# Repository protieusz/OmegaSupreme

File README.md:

# OmegaSupreme
RP2040 integrated components with integrated PMW3360 trackball sensor &amp; PER56 encoder. The OmegaSupreme is inspired by Ariamelon's Kiwano VIK module and jfedor2's RP2040 and PMW3660 module. The RP2040 pins are fully broken out into either pads or ribbon connections. Design this for convienience and easier to design a keyboard pcb around the OmegaSupreme itself.
Current on print by JLCPCB. Cost is a little bit on the pricey side. Around $89 CAD with shipping included. SK6812 mini e was omitted from the assembly to keep the cost down.  Part of the reason behind being pricey was the use of 3 extended parts i.e. 2 ribbon connectors and 1 JSH connector.  [Gerber](https://github.com/protieusz/OmegaSupreme/tree/main/OmegaSupremeRev4) files will be posted once I tested it. As always print at your "OWN RISK".  I do not offer support. You can feel free to modify it as long as you credit me. Thanks.

# Note: Currently there are 2 versions of Omega Supreme. OmegaSupreme USB C & Non USB C Version using a C3 Unified USB C Daughterboard card

# OmegaSupreme got mentioned on https://kbd.news/Starship-Bubu-OmegaSupreme-2184.html

# Update: Nov 13, 2023: OmegaSupreme USB Version.
Uploaded OmegaSupreme USB Version files. This is my preferred OmegaSupreme version. This version's production file will include a converted json file from EasyEDA to KiCad pcb file.  Please print and assembly at your own risk. I have the PCBs printed and tested so it works. No support will be given. Please follow the license when you modify, use, etc. Thanks.

# Extra BOMs:

1 [PMW3360 Sensor for trackball](https://www.aliexpress.com/item/1005005355003386.html?spm=a2g0o.order_list.order_list_main.23.31a51802RLpcrc)

2 [C3 Unified USB C Daughterboard card](https://42keebs.eu/shop/parts/unified-daughterboard-c3-c4/?attribute_version=C3)

3 [M3 3mm standoffs](https://www.aliexpress.com/item/1005004127890102.html?spm=a2g0o.order_list.order_list_main.60.31a51802RLpcrc)

4 [M3 8mm screw, buy 6mm just in case](https://www.aliexpress.com/item/1005003733948224.html?spm=a2g0o.order_list.order_list_main.41.31a51802RLpcrc)

5 [MJ311 or MJ310 steel or ceramic ball bearings for the trackball support holder unit. Steel is slightly noisy and scratchy compared to ceramic. Test it out on your own](https://www.aliexpress.com/item/1005005334424631.html?spm=a2g0o.order_list.order_list_main.66.31a51802RLpcrc)

6 [RGBs SK6812](https://www.aliexpress.com/item/1005003636607308.html?spm=a2g0o.order_list.order_list_main.5.31a51802RLpcrc)

7 [Reset & Boot switches](https://www.aliexpress.com/item/4001317902663.html?spm=a2g0o.order_list.order_list_main.240.31a51802RLpcrc)

# OmegaSupreme USB Version Final Pics:

Back Side

Front & Back Side

# Update: Nov 12, 2023. 
Currently there are 2 versions of Omega Supreme. The Rev 4 with all the extended connectors and a USB C version that does not require a USB C daughterboard card. I printed both versions and I find that Rev 1 is very annoying since it needs a USB C daughterboard card.  Nowadays, the reliability of PCBA and PCB printing from China factories are not that good if you are doing small 5 PCBs prototyping.  In my experience PCBA can be hit and miss.  Even the USB C daughterboard card can be a miss also.  So in order to eliminate headaches, I use the Omega Supreme USB C version where everything is in one place. Easier to diagnostic if shit goes south.

# REV 4 has 2 copper plated holes for the trackball support mount on the PCB which was missed during REV 1 print.  This PCB picture is REV1 without the corrected copper plated mount holes.

# D- and D+ pins are switched so when you attach your usb c daughterboard card, please be caution.

# REV 4 render. I don't have funds to print anymore.

# REV 1

# REV 3 Forgot to add M3 plated mounts for the trackball support and added RGB DOUT, 5v and GND for the last RGB on the OmegaSupreme

# License

</a></p>

You are free to:

Share — copy and redistribute the material in any medium or format

Adapt — remix, transform, and build upon the material

The licensor cannot revoke these freedoms as long as you follow the license terms.
Under the following terms:

Attribution — You must give appropriate credit, provide a link to the license, and indicate if changes were made. You may do so in any reasonable manner, but not in any way that suggests the licensor endorses you or your use.

NonCommercial — You may not use the material for commercial purposes.

ShareAlike — If you remix, transform, or build upon the material, you must distribute your contributions under the same license as the original.

No additional restrictions — You may not apply legal terms or technological measures that legally restrict others from doing anything the license permits.

OmegaSupreme by ProtieusKeebs is licensed under [CC BY-NC-SA 4.0](https://creativecommons.org/licenses/by-nc-sa/4.0/?ref=chooser-v1)

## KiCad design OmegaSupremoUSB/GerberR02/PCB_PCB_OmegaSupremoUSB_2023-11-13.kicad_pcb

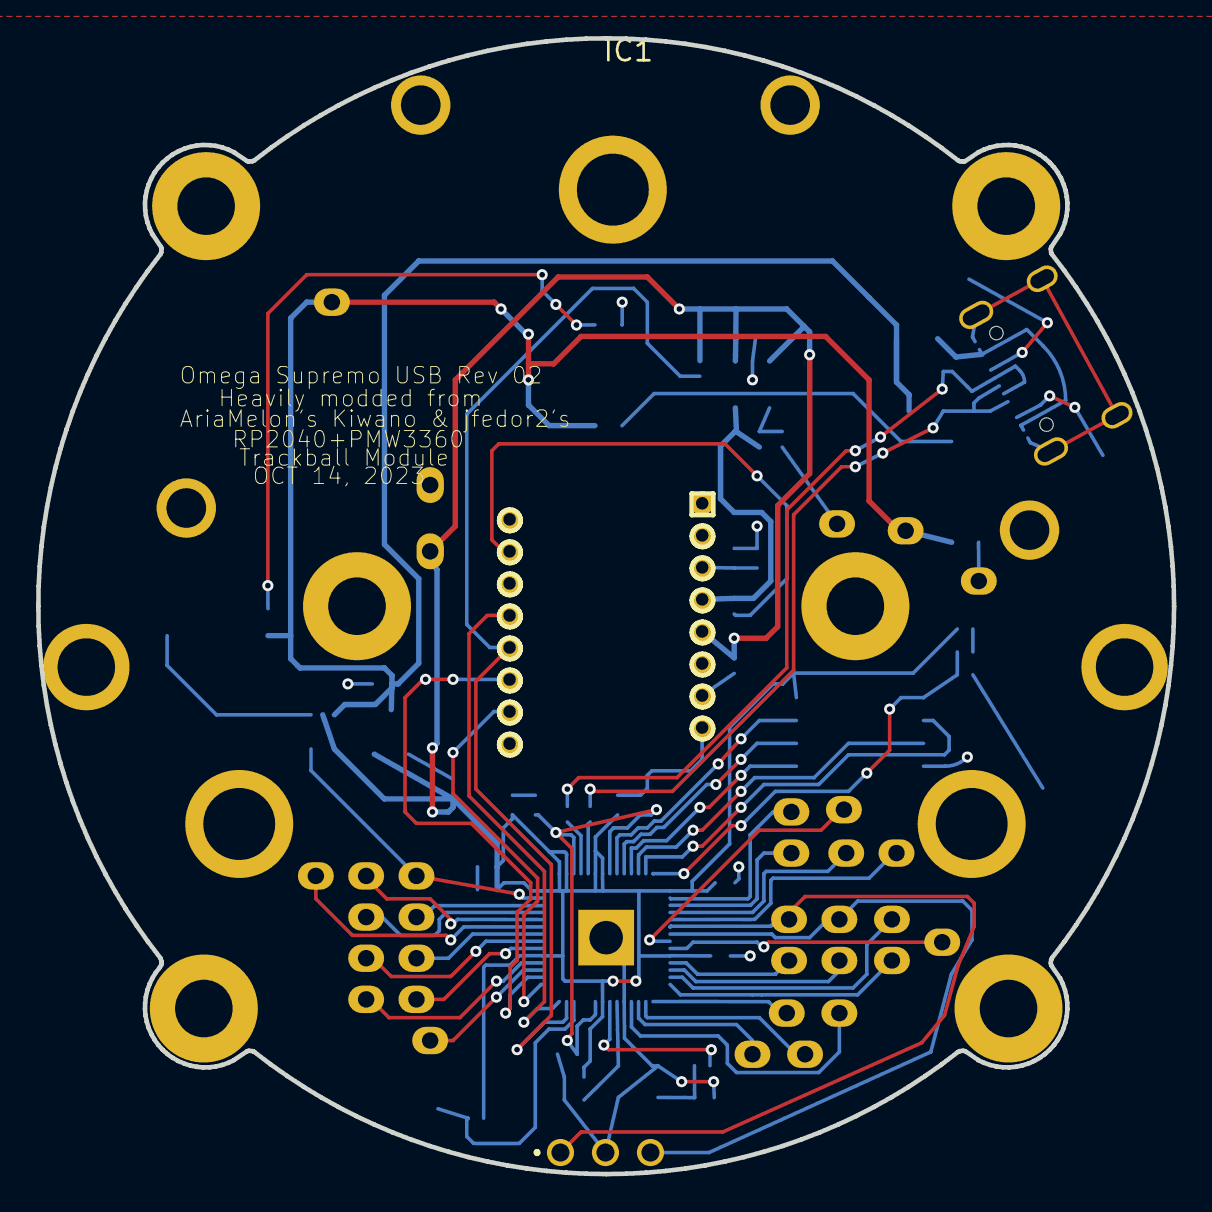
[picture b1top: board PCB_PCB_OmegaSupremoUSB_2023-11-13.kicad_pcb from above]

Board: 2 copper layers, 63.1 x 63.1 mm, 88 parts (0 on the bottom side), 62 nets.

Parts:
5V: NO; PIN 1-PIN
+3V3, +5V: NO; PIN 1-PIN
C1, C2, C5, C6, C9: 1uF; C0402
C3, C4: 22pF; C0402
C7, C10, C11, C12, C13, C14, C15, C16, C18: 100nF; C0402
C8: 10uF; C0402
C17, C19, C20: 4.7uF; C0402
COL0, COL1, COL2, COL3, COL4, COL5, COL6, COL7, COL8, COL9: NO; PIN 1-PIN
D11: PRTR5V0U2X,215; SOT-143_L2.9-W1.3-P1.92-LS2.3-BR
DOUT: NO; PIN 1-PIN
ENCA: NO; PIN 1-PIN
ENCB: NO; PIN 1-PIN
F1: BSMD0805-020-15V; F0805
GND1, GND2: NO; PIN 1-PIN
GP6, GP12, GP13, GP14, GP15, GP25, GP26, GP27, GP29: NO; PIN 1-PIN
IC1: PER561-P115-N0015; PER561P115N0015
R1, R2, R3, R4, R5: 5.1kΩ; R0402
R6, R7: 1kΩ; R0402
R8, R9: 27Ω; R0402
R10, R12, R13: 10kΩ; R0402
R11: 39Ω; R0402
R14: 15kΩ; R0402
RGBMCU: NO; PIN 1-PIN
ROW0, ROW1, ROW2, ROW3: NO; PIN 1-PIN
U1: RESET; RESET SWITCH
U2: BOOT; RESET SWITCH
U3: W25Q128JVSIQTR; SOIC-8_L5.3-W5.3-P1.27-LS8.0-BL
U4: RP2040; LQFN-56_L7.0-W7.0-P0.4-EP
U5: XC6206P332MR; SOT-23-3_L2.9-W1.6-P1.90-LS2.8-BR
U6: SN74LVC1T45QDCKRQ1; SC-70-6_L2.0-W1.3-P0.65-LS2.1-BR
U7: PMW3360DM-T2QU; PMW3360DM-T2QU.PACK
U8: AP2127K-ADJTRG1; SOT-23-5_L3.0-W1.7-P0.95-LS2.8-BR
U9, U13, U14, U15, U16, U17: NO; MT_HOLE-3MM
U10, U11, U12: SK6812MINI-E_C5149201; LED-SMD_L3.2-W2.8-TR
USBC1: TYPE-C-31-M-12; USB-C_SMD-TYPE-C-31-M-12
X1: 12MHz; OSC-SMD_4P-L3.2-W2.5-BL

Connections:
+1V1: C6.2, C7.2, C13.2, U4.23, U4.45, U4.50
+2V: C20.2, R11.2, R14.2, U7.4, U8.5
+3V3: +3V3.1, C2.2, C5.2, C8.2, C9.2, C10.2, C11.2, C12.2, C14.2, C15.2, C16.2, C19.2, R3.2, R4.2, R10.2, R12.2, U3.8, U4.1, U4.10, U4.22, U4.33, U4.42, U4.43, U4.44, U4.48, U4.49, U5.2, U6.1, U6.5, U7.5, U8.1, U8.3
+5V: 5V.1, +5V.1, C1.2, D11.4, F1.2, U5.3, U6.6, U10.1, U11.1, U12.1
C4_1: C4.1, R7.1, X1.1
C18_1: C17.1, C18.1, U7.3
COL0: COL0.1, U4.36
COL1: COL1.1, U4.35
COL2: COL2.1, U4.34
COL3: COL3.1, U4.32
COL4: COL4.1, U4.31
COL5: COL5.1, U4.2
COL6: COL6.1, U4.8
COL7: COL7.1, U4.5
COL8: COL8.1, U4.4
COL9: COL9.1, U4.3
CS: U4.28, U7.13
D+: D11.3, R8.2, USBC1.A6, USBC1.B6
D-: D11.2, R9.2, USBC1.A7, USBC1.B7
DOUT_1: DOUT.1, U12.2
ENCA: ENCA.1, IC1.1, U4.6
ENCB: ENCB.1, IC1.3, U4.7
GND: C1.1, C2.1, C3.1, C4.2, C5.1, C6.1, C7.1, C8.1, C9.1, C10.1, C11.1, C12.1, C13.1, C14.1, C15.1, C16.1, C17.2, C18.2, C19.1, C20.1, D11.1, GND1.1, GND2.1, IC1.2, R1.2, R2.1, R13.1, U1.1, U2.1, U3.4, U4.19, U4.57, U5.1, U6.2, U7.8, U8.2, U10.3, U11.3, U12.3, USBC1.0, USBC1.1, USBC1.2, USBC1.3, USBC1.A1, USBC1.A12, USBC1.B1, USBC1.B12, X1.2, X1.4
GP6: GP6.1, U4.9
GP12: GP12.1, U4.15
GP13: GP13.1, U4.16
GP14: GP14.1, U4.17
GP15: GP15.1, U4.18
GP25: GP25.1, U4.37
GP26: GP26.1, U4.38
GP27: GP27.1, U4.39
GP29: GP29.1, U4.40
MISO: R12.1, U4.27, U7.12
MOSI: U4.30, U7.11
Q_CLK: U3.6, U4.52
Q_IO0: U3.5, U4.53
Q_IO1: U3.2, U4.55
Q_IO2: U3.3, U4.54
Q_IO3: U3.7, U4.51
Q_SEL: R5.1, R6.2, U3.1, U4.56
R5_2: R4.1, R5.2
R10_1: R10.1, U7.7
R11_1: R11.1, U7.15
R14_1: R13.2, R14.1, U8.4
RESET: R3.1, U1.2, U4.26
RGB: U6.4, U10.4
RGBMCU: RGBMCU.1, U4.41, U6.3
ROW0: ROW0.1, U4.11
ROW1: ROW1.1, U4.12
ROW2: ROW2.1, U4.13
ROW3: ROW3.1, U4.14
SCK: U4.29, U7.10
U2_2: R6.1, U2.2
U4_46: R9.1, U4.46
U4_47: R8.1, U4.47
U10_2: U10.2, U11.4
U11_2: U11.2, U12.4
USBC1_A5: R1.1, USBC1.A5
USBC1_B5: R2.2, USBC1.B5
VBUS: F1.1, USBC1.A4, USBC1.A9, USBC1.B4, USBC1.B9
XIN: C3.2, U4.20, X1.3
XOUT: R7.2, U4.21

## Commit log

2023-10-11 Update LICENSE
2023-11-12 Latest Revision that has the fixed mounting screws
2023-11-12 Updated to REV 3
2023-11-12 REV4
2023-11-13 OmegaSupreme USB Production Files

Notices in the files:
README.md:
https://mirrors.creativecommons.org/presskit/icons/cc.svg?ref=chooser-v1https://mirrors.creativecommons.org/presskit/icons/by.svg?ref=chooser-v1https://mirrors.creativecommons.org/presskit/icons/nc.svg?ref=chooser-v1
